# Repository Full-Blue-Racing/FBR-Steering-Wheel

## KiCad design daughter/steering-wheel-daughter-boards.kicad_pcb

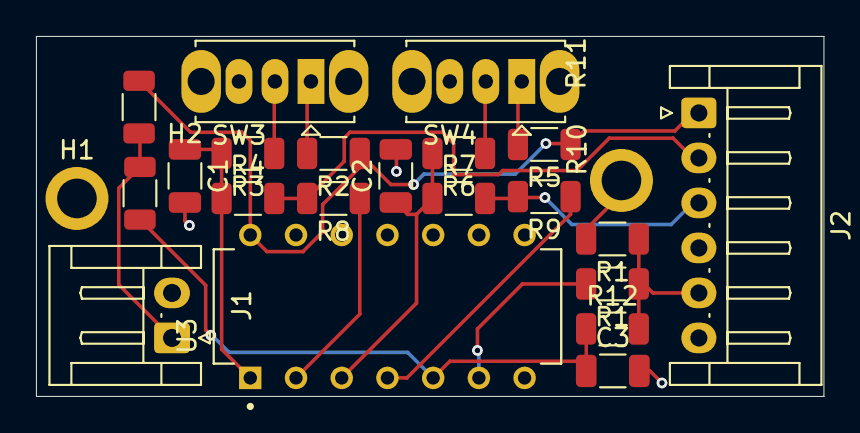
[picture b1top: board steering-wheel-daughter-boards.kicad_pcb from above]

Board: 2 copper layers, 43.8 x 20.0 mm, 23 parts (0 on the bottom side), 16 nets.

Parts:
C1, C2, C3: C; C_1206_3216Metric
H1, H2: MountingHole_Pad; MountingHole_2.2mm_M2_ISO7380_Pad
J1: Conn_01x02_Socket; JST_EH_S2B-EH_1x02_P2.50mm_Horizontal
J2: Conn_01x06_Socket; JST_EH_S6B-EH_1x06_P2.50mm_Horizontal
R1: 10k; R_1206_3216Metric
R1#2, R8, R9: 0; R_1206_3216Metric
R2, R3, R4, R5, R6, R7, R10, R11, R12: R; R_1206_3216Metric
SW3, SW4: SW_SPDT; SW_Slide_SPDT_Straight_CK_OS102011MS2Q
U3: 74HC14; DIP794W45P254L1930H508Q14

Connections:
+3V3: J2.1, R2.1, R5.1, R10.1, U3.14 (VCC)
/PAD_RTN: J2.5, R1.1, R1#2.1, R12.2
BTN1: J2.2, R4.2, R8.2
BTN2: J2.3, R7.2, R9.2
GND: C1.2, C2.2, C3.2, H1.1, H2.1, J1.2, J2.6, R1.2, SW3.3 (C), SW4.3 (C), U3.7 (GND)
unnamed: C1.1, R3.2, R4.1, U3.1
unnamed: C2.1, R6.2, R7.1, U3.3
unnamed: C3.1, R11.2, R12.1, U3.5
unnamed: J1.1, R10.2, R11.1
unnamed: R1#2.2, U3.6
unnamed: R8.1, U3.2
unnamed: R9.1, U3.4
unnamed: R2.2, SW3.1 (A)
unnamed: R3.1, SW3.2 (B)
unnamed: R5.2, SW4.1 (A)
unnamed: R6.1, SW4.2 (B)

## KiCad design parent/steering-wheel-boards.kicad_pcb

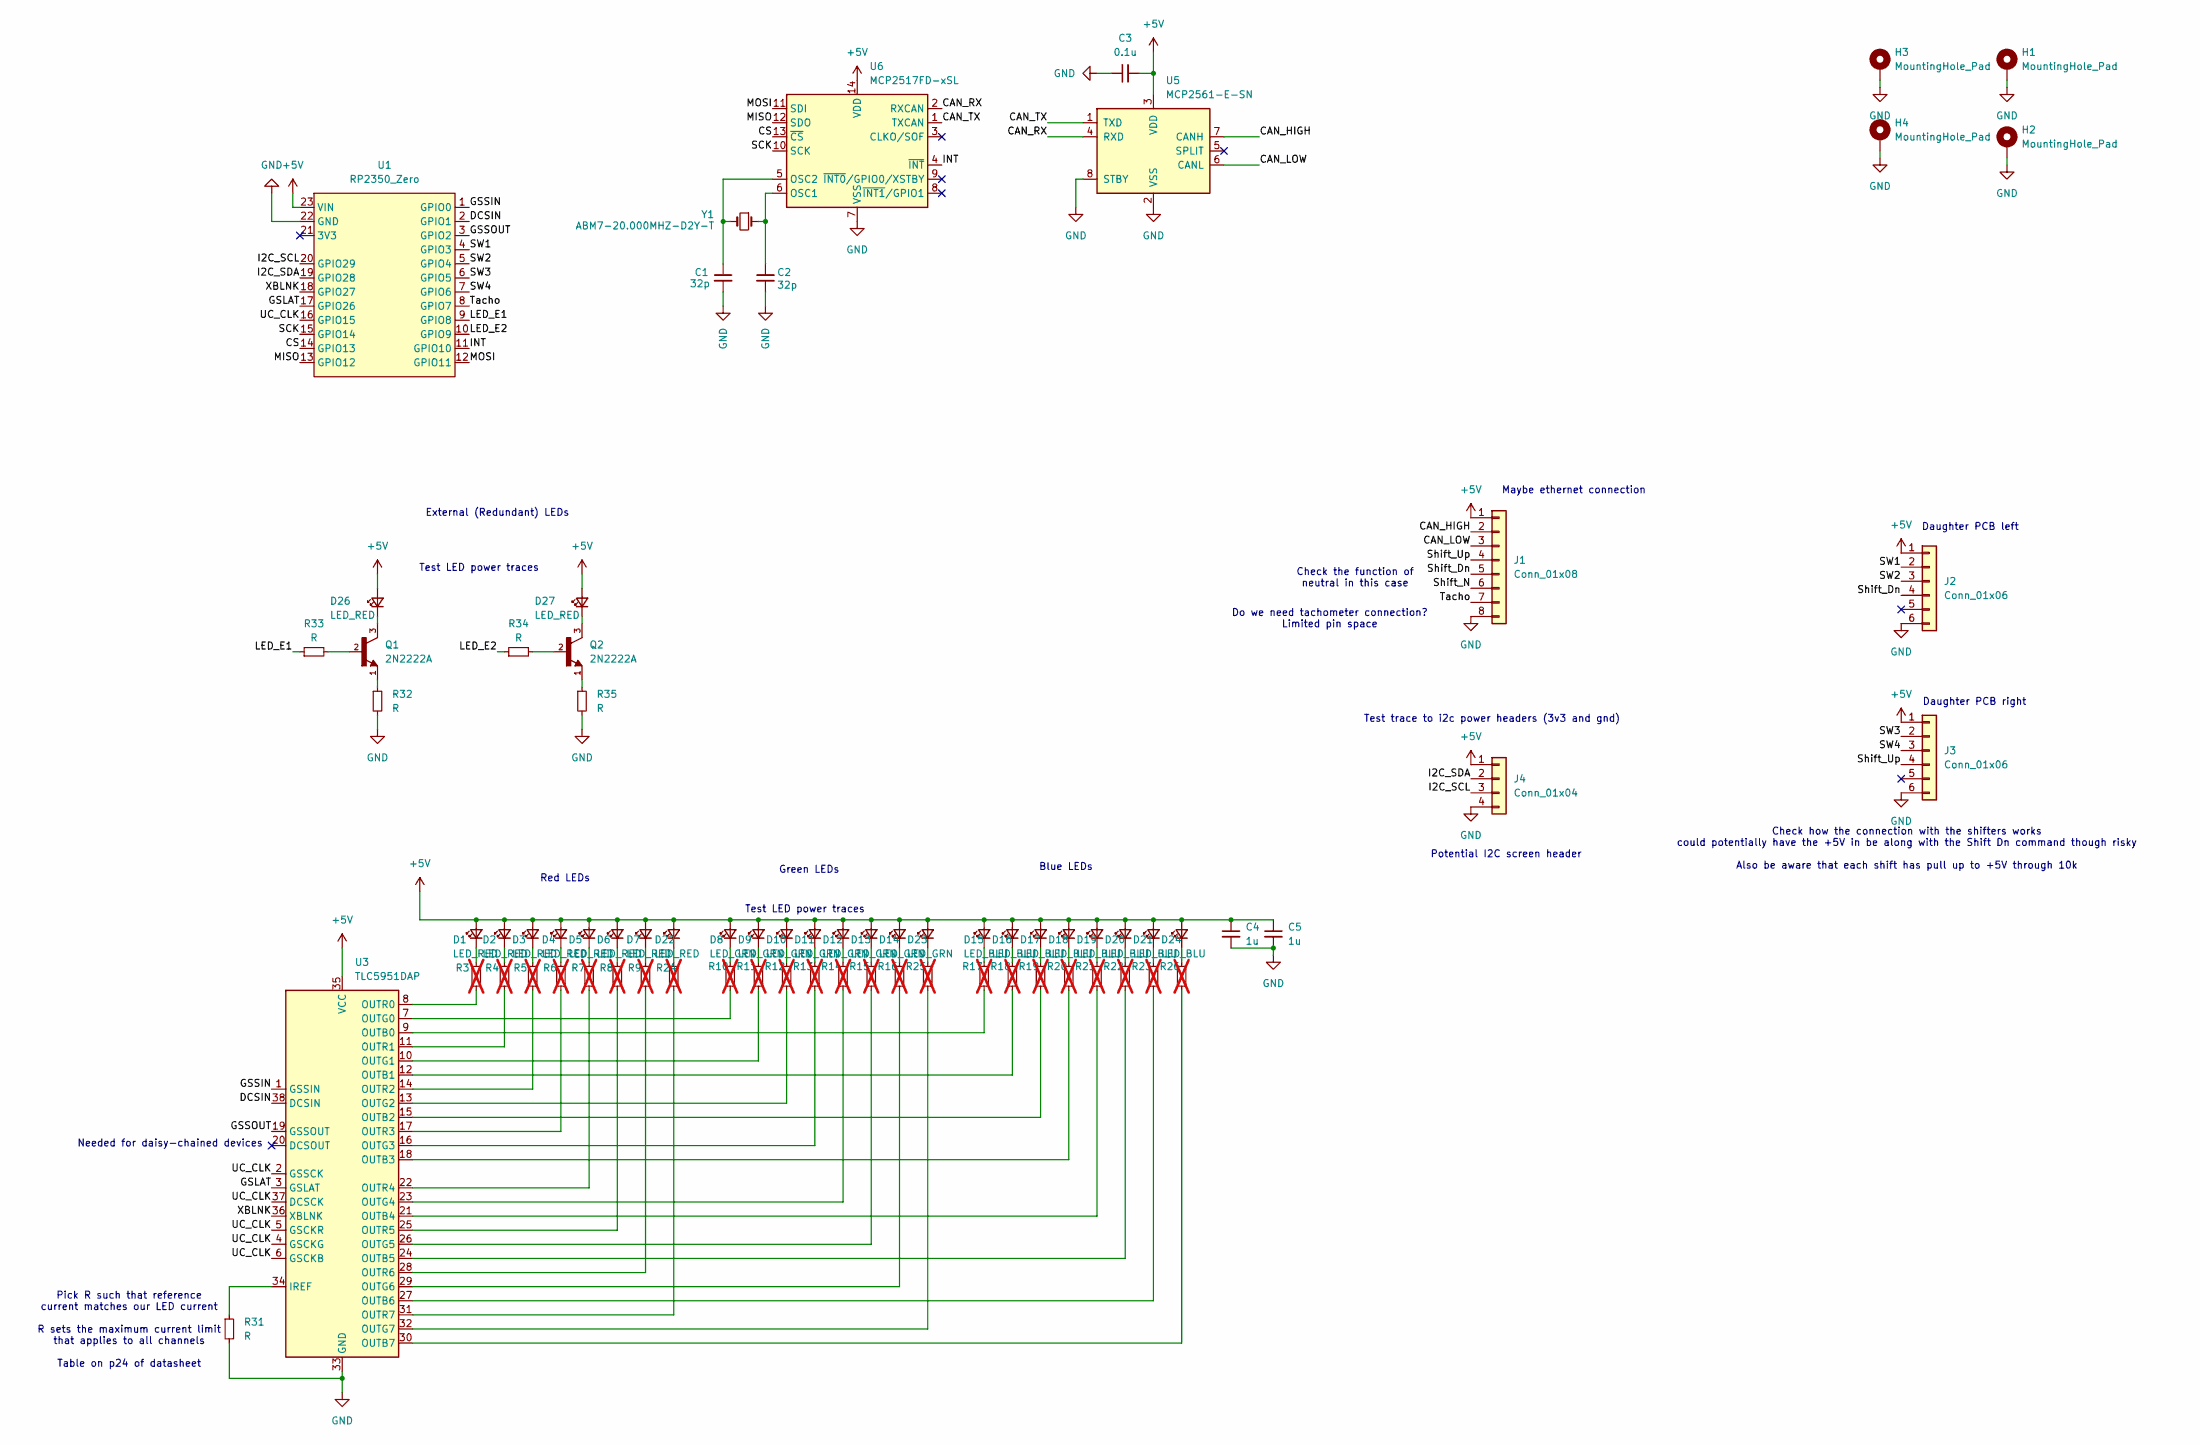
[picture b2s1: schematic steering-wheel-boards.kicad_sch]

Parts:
C1, C2: 32p; CAP_RCER72A105K2DBH03A
C3: 0.1u; CAP_RCER72A105K2DBH03A
C4, C5: 1u; CAP_RCER72A105K2DBH03A
D1, D2, D3, D4, D5, D6, D7, D22, D26, D27: LED_RED; 5990K80107F
D8, D9, D10, D11, D12, D13, D14, D23: LED_GRN; 5990K80107F
D15, D16, D17, D18, D19, D20, D21, D24: LED_BLU; 5990K80107F
H1, H2, H3, H4: MountingHole_Pad; MountingHole_3mm_Pad
J1: Conn_01x08; RJ45_BEL_SS74301-00x_Vertical
J2, J3: Conn_01x06; JST_EH_S6B-EH_1x06_P2.50mm_Horizontal
J4: Conn_01x04; JST_EH_B4B-EH-A_1x04_P2.50mm_Vertical
Q1, Q2: 2N2222A; PARTREV N/A
R3, R4, R5, R6, R7, R8, R9, R10, R11, R12, R13, R14, R15, R16, R17, R18, R19, R20, R21, R22, R23, R24, R25, R26: R_Small; R_Axial_DIN0204_L3.6mm_D1.6mm_P5.08mm_Horizontal; not fitted
R31, R32, R33, R34, R35: R; R_Axial_DIN0204_L3.6mm_D1.6mm_P5.08mm_Horizontal
U1: RP2350_Zero
U3: TLC5951DAP; HTSSOP-38-1EP_6.1x12.5mm_P0.65mm_EP5.2x12.5mm_Mask3.39x6.35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
U5: MCP2561-E-SN; SOIC-8_3.9x4.9mm_P1.27mm
U6: MCP2517FD-xSL; SOIC-14_3.9x8.7mm_P1.27mm
Y1: ABM7-20.000MHZ-D2Y-T; Crystal_SMD_Abracon_ABM7-2Pin_6.0x3.5mm

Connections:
+5V: C3.2, C4.1, C5.1, D1.2 (A), D2.2 (A), D3.2 (A), D4.2 (A), D5.2 (A), D6.2 (A), D7.2 (A), D8.2 (A), D9.2 (A), D10.2 (A), D11.2 (A), D12.2 (A), D13.2 (A), D14.2 (A), D15.2 (A), D16.2 (A), D17.2 (A), D18.2 (A), D19.2 (A), D20.2 (A), D21.2 (A), D22.2 (A), D23.2 (A), D24.2 (A), D26.2 (A), D27.2 (A), J1.1, J2.1, J3.1, J4.1, U1.23 (VIN), U3.35 (VCC), U5.3 (VDD), U6.14 (VDD)
/CAN_HIGH: J1.2, U5.7 (CANH)
/CAN_LOW: J1.3, U5.6 (CANL)
/CAN_RX: U5.4 (RXD), U6.2 (RXCAN)
/CAN_TX: U5.1 (TXD), U6.1 (TXCAN)
/CS: U1.14 (GPIO13), U6.13 (~CS)
/DCSIN: U1.2 (GPIO1), U3.38 (DCSIN)
/GSLAT: U1.17 (GPIO26), U3.3 (GSLAT)
/GSSIN: U1.1 (GPIO0), U3.1 (GSSIN)
/GSSOUT: U1.3 (GPIO2), U3.19 (GSSOUT)
/I2C_SCL: J4.3, U1.20 (GPIO29)
/I2C_SDA: J4.2, U1.19 (GPIO28)
/INT: U1.11 (GPIO10), U6.4 (~INT)
/LED_E1: R33.1, U1.9 (GPIO8)
/LED_E2: R34.1, U1.10 (GPIO9)
/MISO: U1.13 (GPIO12), U6.12 (SDO)
/MOSI: U1.12 (GPIO11), U6.11 (SDI)
/SCK: U1.15 (GPIO14), U6.10 (SCK)
/SW1: J2.2, U1.4 (GPIO3)
/SW2: J2.3, U1.5 (GPIO4)
/SW3: J3.2, U1.6 (GPIO5)
/SW4: J3.3, U1.7 (GPIO6)
/Shift_Dn: J1.5, J2.4
/Shift_N: J1.6
/Shift_Up: J1.4, J3.4
/Tacho: J1.7, U1.8 (GPIO7)
/UC_CLK: U1.16 (GPIO15), U3.2 (GSSCK), U3.4 (GSCKG), U3.5 (GSCKR), U3.6 (GSCKB), U3.37 (DCSCK)
/XBLNK: U1.18 (GPIO27), U3.36 (XBLNK)
GND: C1.2, C2.2, C3.1, C4.2, C5.2, H1.1, H2.1, H3.1, H4.1, J1.8, J2.6, J3.6, J4.4, R31.2, R32.2, R35.2, U1.22 (GND), U3.33 (GND), U3.39 (GND), U5.2 (VSS), U5.8 (STBY), U6.7 (VSS)
unnamed: D1.1 (K), R3.1
unnamed: D2.1 (K), R4.1
unnamed: D3.1 (K), R5.1
unnamed: D4.1 (K), R6.1
unnamed: D5.1 (K), R7.1
unnamed: D6.1 (K), R8.1
unnamed: D7.1 (K), R9.1
unnamed: D8.1 (K), R10.1
unnamed: D9.1 (K), R11.1
unnamed: D10.1 (K), R12.1
unnamed: D11.1 (K), R13.1
unnamed: D12.1 (K), R14.1
unnamed: D13.1 (K), R15.1
unnamed: D14.1 (K), R16.1
unnamed: D15.1 (K), R17.1
unnamed: D16.1 (K), R18.1
unnamed: D17.1 (K), R19.1
unnamed: D18.1 (K), R20.1
unnamed: D19.1 (K), R21.1
unnamed: D20.1 (K), R22.1
unnamed: D21.1 (K), R23.1
unnamed: D22.1 (K), R24.1
unnamed: D23.1 (K), R25.1
unnamed: D24.1 (K), R26.1
unnamed: D26.1 (K), Q1.3
unnamed: D27.1 (K), Q2.3
unnamed: Q1.1, R32.1
unnamed: Q1.2, R33.2
unnamed: Q2.1, R35.1
unnamed: Q2.2, R34.2
unnamed: R31.1, U3.34 (IREF)
unnamed: R17.2, U3.9 (OUTB0)
unnamed: R18.2, U3.12 (OUTB1)
unnamed: R19.2, U3.15 (OUTB2)
unnamed: R20.2, U3.18 (OUTB3)
unnamed: R21.2, U3.21 (OUTB4)
unnamed: R22.2, U3.24 (OUTB5)
unnamed: R23.2, U3.27 (OUTB6)
unnamed: R26.2, U3.30 (OUTB7)
unnamed: R10.2, U3.7 (OUTG0)
unnamed: R11.2, U3.10 (OUTG1)
unnamed: R12.2, U3.13 (OUTG2)
unnamed: R13.2, U3.16 (OUTG3)
unnamed: R14.2, U3.23 (OUTG4)
unnamed: R15.2, U3.26 (OUTG5)
unnamed: R16.2, U3.29 (OUTG6)
unnamed: R25.2, U3.32 (OUTG7)
unnamed: R3.2, U3.8 (OUTR0)
unnamed: R4.2, U3.11 (OUTR1)
unnamed: R5.2, U3.14 (OUTR2)
unnamed: R6.2, U3.17 (OUTR3)
unnamed: R7.2, U3.22 (OUTR4)
unnamed: R8.2, U3.25 (OUTR5)
unnamed: R9.2, U3.28 (OUTR6)
unnamed: R24.2, U3.31 (OUTR7)
unnamed: C2.1, U6.6 (OSC1), Y1.1
unnamed: C1.1, U6.5 (OSC2), Y1.2

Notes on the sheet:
Red LEDs
Do we need tachometer connection? Limited pin space
Pick R such that reference current matches our LED current R sets the maximum current limit that applies to all channels Table on p24 of datasheet
Test trace to i2c power headers (3v3 and gnd)
Maybe ethernet connection
Check the function of neutral in this case
Test LED power traces
External (Redundant) LEDs
Daughter PCB left
Potential I2C screen header
Needed for daisy-chained devices
Blue LEDs
Check how the connection with the shifters works could potentially have the +5V in be along with the Shift Dn command though risky Also be aware that each shift has pull up to +5V through 10k
Green LEDs
Daughter PCB right

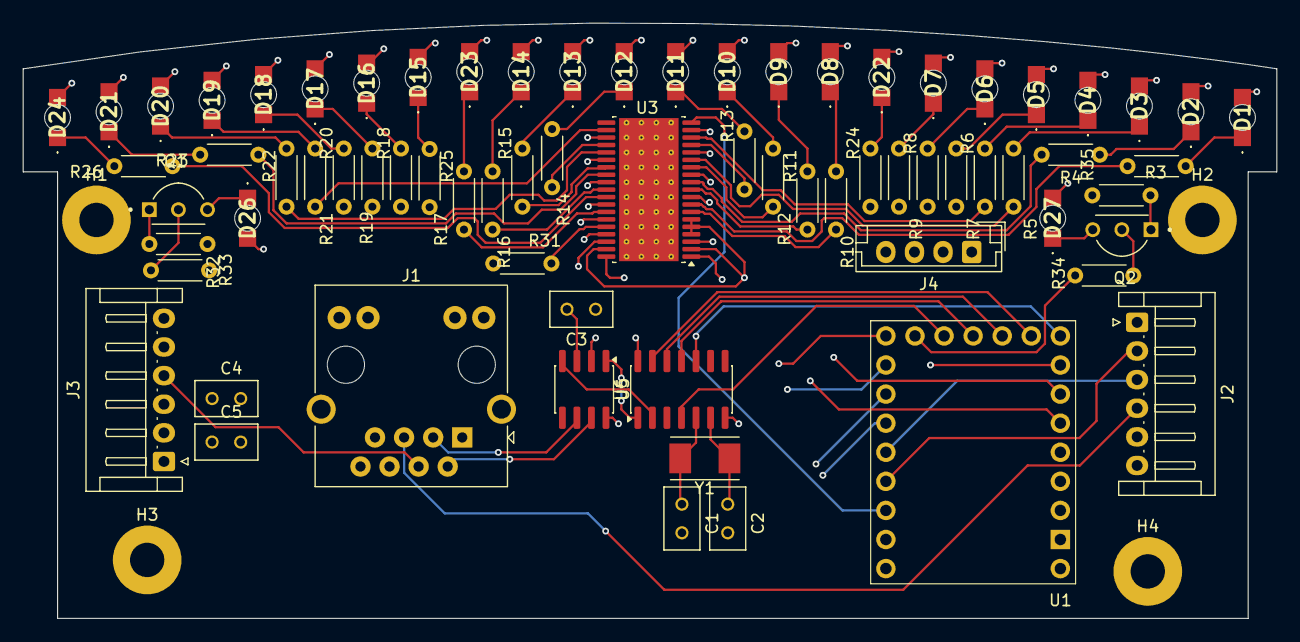
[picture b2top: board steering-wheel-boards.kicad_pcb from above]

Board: 4 copper layers, 109.5 x 52.0 mm, 75 parts (0 on the bottom side), 85 nets.

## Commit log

2026-03-21 Upload to GitHub
2026-03-21 Upload PCB file
2026-03-21 Replace ESP32 with RP2350 Zero
2026-03-28 Assign footprints
2026-03-28 Route Steering Wheel
2026-03-29 Change input voltage to +5V
2026-04-15 Create KiCAD workflow
2026-04-17 Fix DRC errors
